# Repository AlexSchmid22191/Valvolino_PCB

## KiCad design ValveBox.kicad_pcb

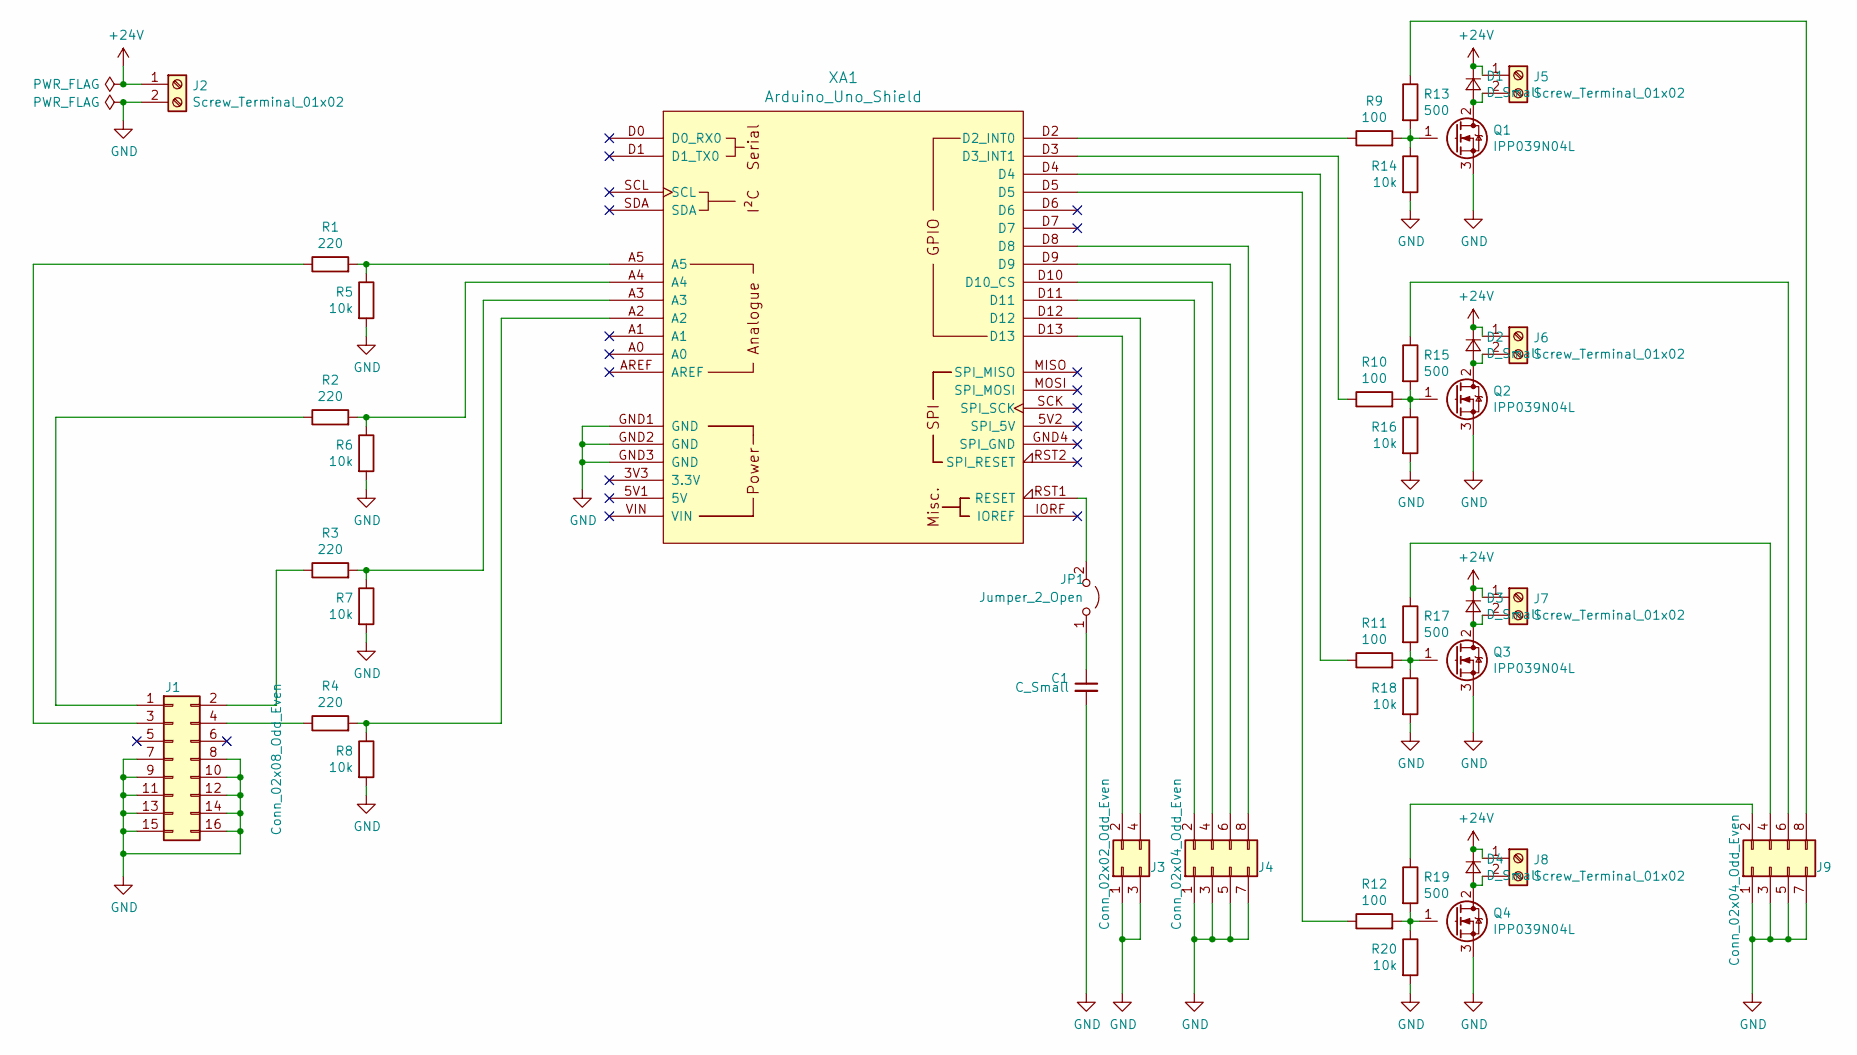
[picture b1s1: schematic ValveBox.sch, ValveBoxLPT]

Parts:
C1: C_Small; C_0603_1608Metric_Pad1.05x0.95mm_HandSolder
D1, D2, D3, D4: D_Small; D_SMA_Handsoldering
J1: Conn_02x08_Odd_Even; IDC_08x02
J2, J5, J6, J7, J8: Screw_Terminal_01x02; RS_Screw_Term_x2
J3: Conn_02x02_Odd_Even; PinHeader_2x02_P2.54mm_Vertical
J4, J9: Conn_02x04_Odd_Even; IDC_04x02
JP1: Jumper_2_Open; PinHeader_1x02_P2.54mm_Vertical
Q1, Q2, Q3, Q4: IPP039N04L; TO-220-3_Vertical
R1, R2, R3, R4: 220; R_0603_1608Metric_Pad1.05x0.95mm_HandSolder
R5, R6, R7, R8, R14, R16, R18, R20: 10k; R_0603_1608Metric_Pad1.05x0.95mm_HandSolder
R9, R10, R11, R12: 100; R_0603_1608Metric_Pad1.05x0.95mm_HandSolder
R13, R15, R17, R19: 500; R_0603_1608Metric_Pad1.05x0.95mm_HandSolder
XA1: Arduino_Uno_Shield; Arduino_Uno_Shield_mod

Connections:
+24V: D1.1 (K), D2.1 (K), D3.1 (K), D4.1 (K), J2.1, J5.1, J6.1, J7.1, J8.1
GND: C1.2, J1.7, J1.8, J1.9, J1.10, J1.11, J1.12, J1.13, J1.14, J1.15, J1.16, J2.2, J3.1, J3.3, J4.1, J4.3, J4.5, J4.7, J9.1, J9.3, J9.5, J9.7, Q1.3 (S), Q2.3 (S), Q3.3 (S), Q4.3 (S), R5.2, R6.2, R7.2, R8.2, R14.2, R16.2, R18.2, R20.2, XA1.GND1 (GND), XA1.GND2 (GND), XA1.GND3 (GND)
unnamed: C1.1, JP1.1 (A)
unnamed: D1.2 (A), J5.2, Q1.2 (D)
unnamed: D2.2 (A), J6.2, Q2.2 (D)
unnamed: D3.2 (A), J7.2, Q3.2 (D)
unnamed: D4.2 (A), J8.2, Q4.2 (D)
unnamed: J1.1, R2.1
unnamed: J1.2, R3.1
unnamed: J1.3, R1.1
unnamed: J1.4, R4.1
unnamed: J3.2, XA1.D13
unnamed: J3.4, XA1.D12
unnamed: J4.2, XA1.D11
unnamed: J4.4, XA1.D10 (D10_CS)
unnamed: J4.6, XA1.D9
unnamed: J4.8, XA1.D8
unnamed: J9.2, R19.1
unnamed: J9.4, R17.1
unnamed: J9.6, R15.1
unnamed: J9.8, R13.1
unnamed: JP1.2 (B), XA1.RST1 (RESET)
unnamed: Q1.1 (G), R9.2, R13.2, R14.1
unnamed: Q2.1 (G), R10.2, R15.2, R16.1
unnamed: Q3.1 (G), R11.2, R17.2, R18.1
unnamed: Q4.1 (G), R12.2, R19.2, R20.1
unnamed: R1.2, R5.1, XA1.A5
unnamed: R2.2, R6.1, XA1.A4
unnamed: R3.2, R7.1, XA1.A3
unnamed: R4.2, R8.1, XA1.A2
unnamed: R9.1, XA1.D2 (D2_INT0)
unnamed: R10.1, XA1.D3 (D3_INT1)
unnamed: R11.1, XA1.D4
unnamed: R12.1, XA1.D5

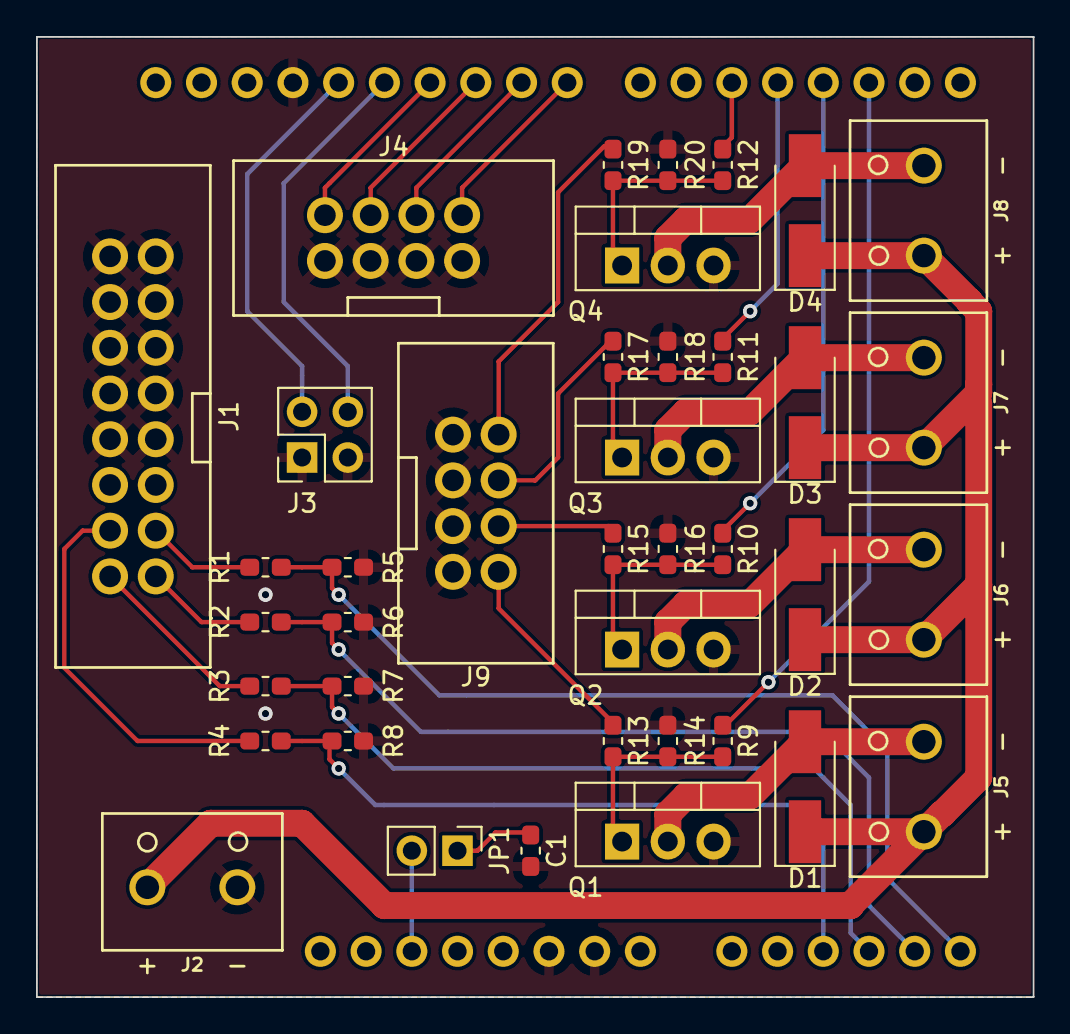
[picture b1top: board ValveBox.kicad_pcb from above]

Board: 2 copper layers, 55.4 x 53.3 mm, 40 parts (0 on the bottom side), 34 nets.
